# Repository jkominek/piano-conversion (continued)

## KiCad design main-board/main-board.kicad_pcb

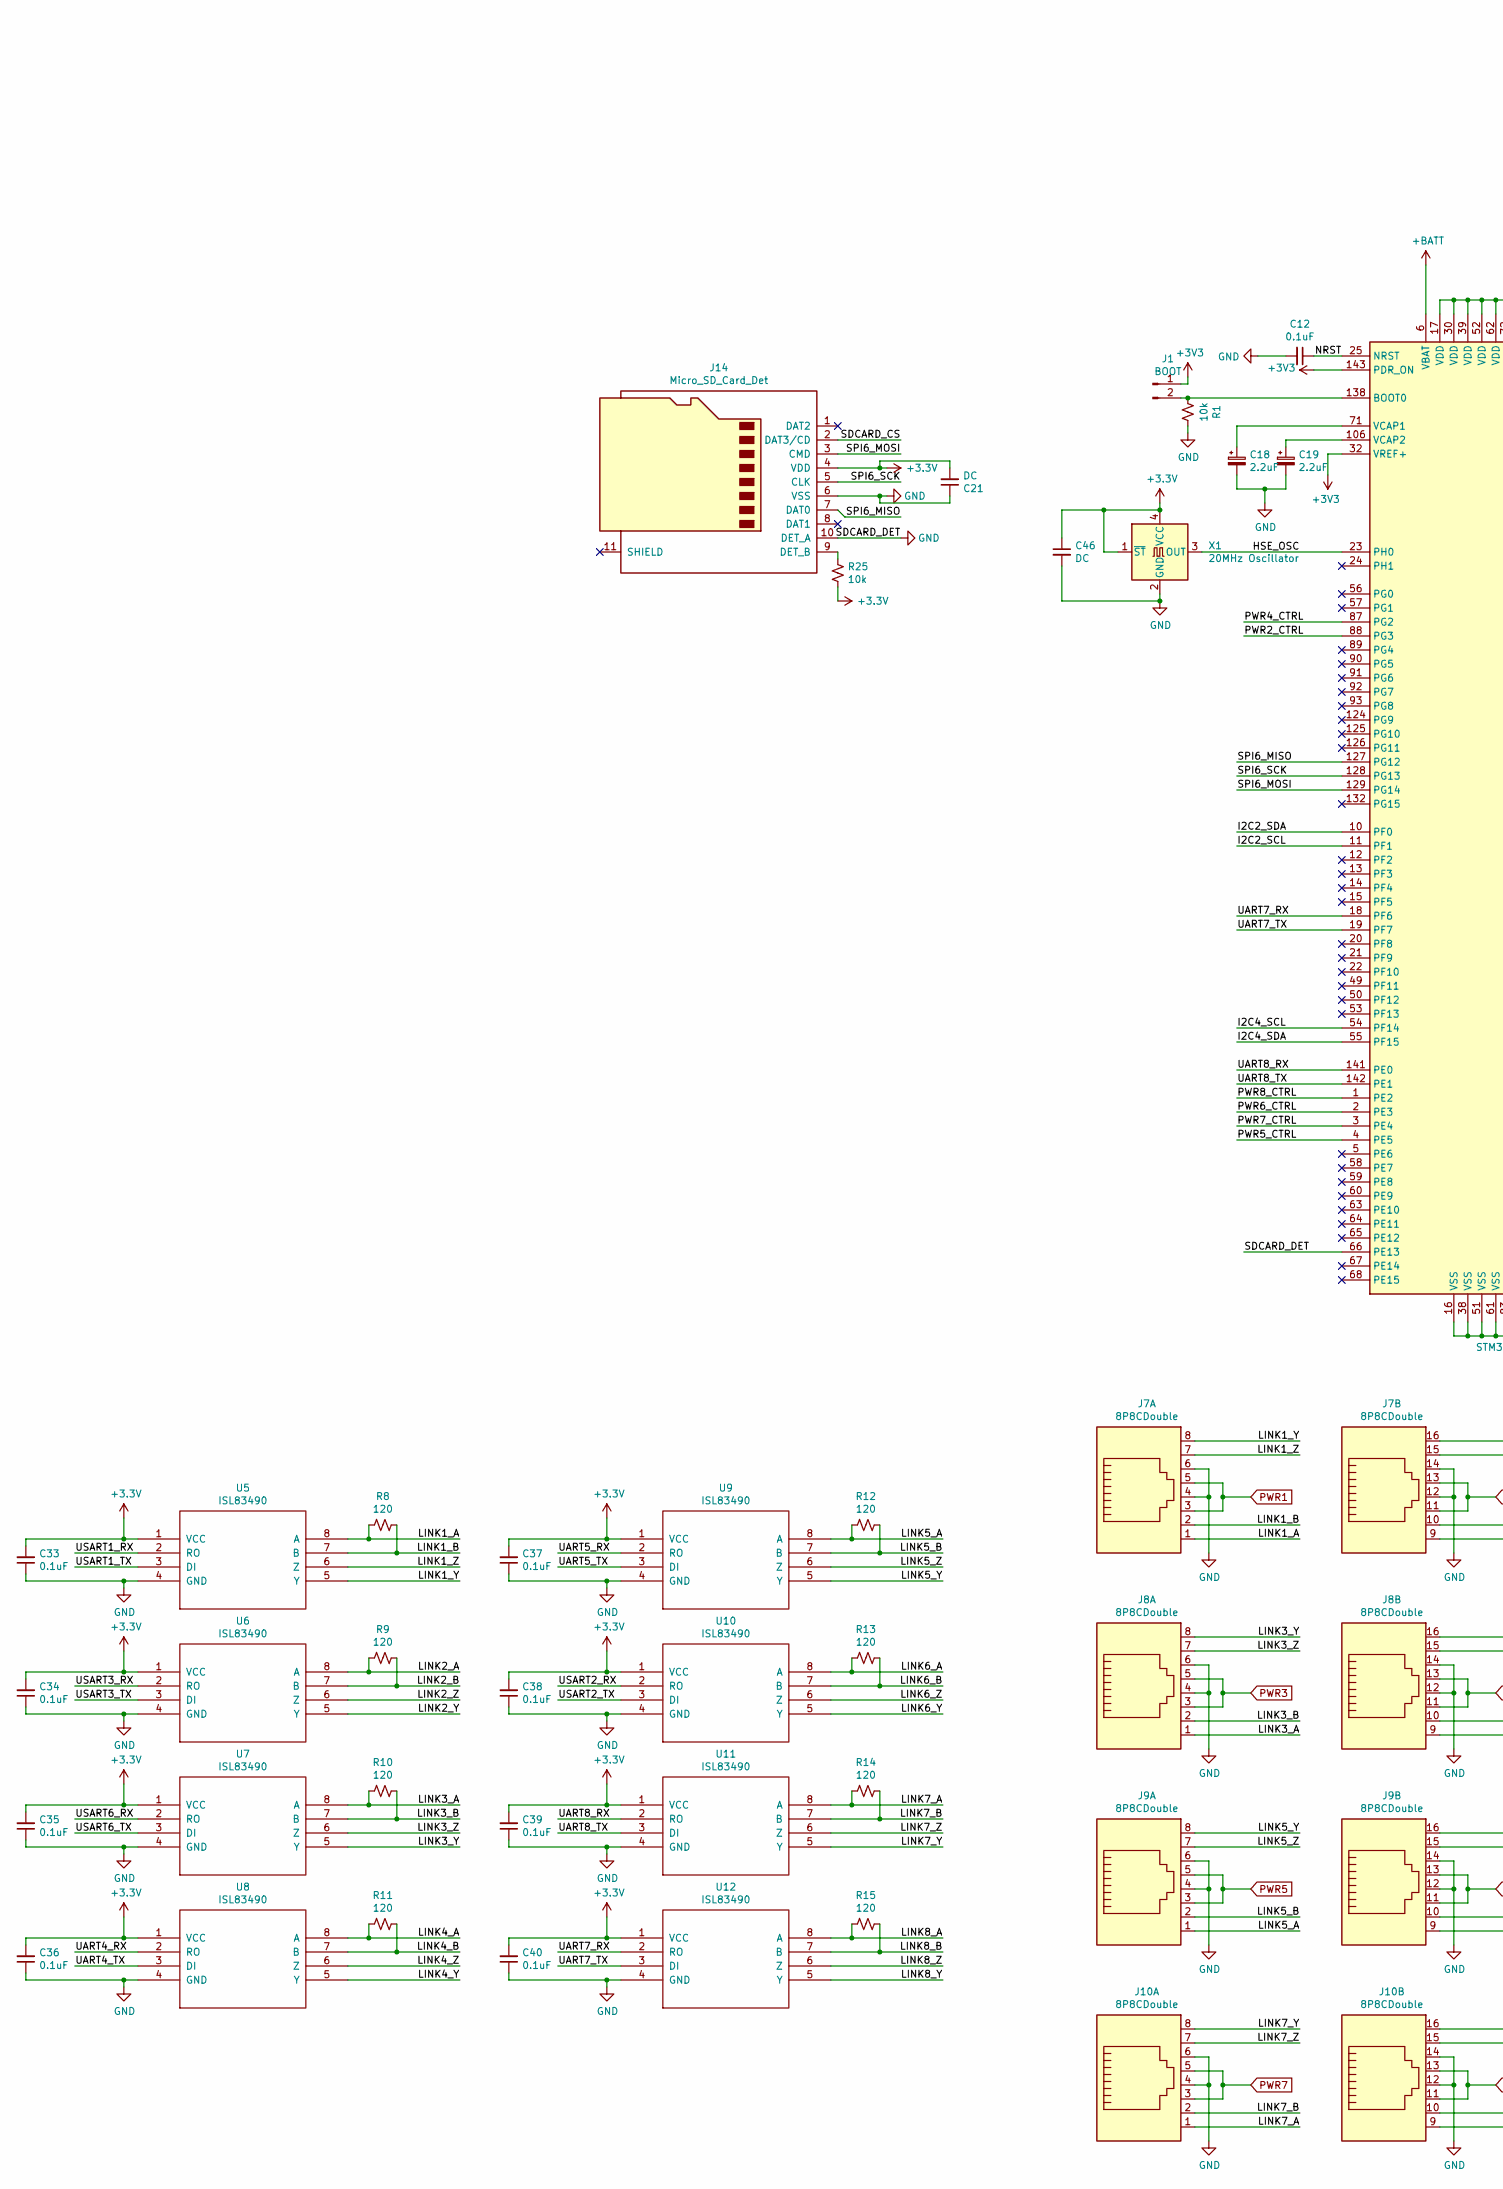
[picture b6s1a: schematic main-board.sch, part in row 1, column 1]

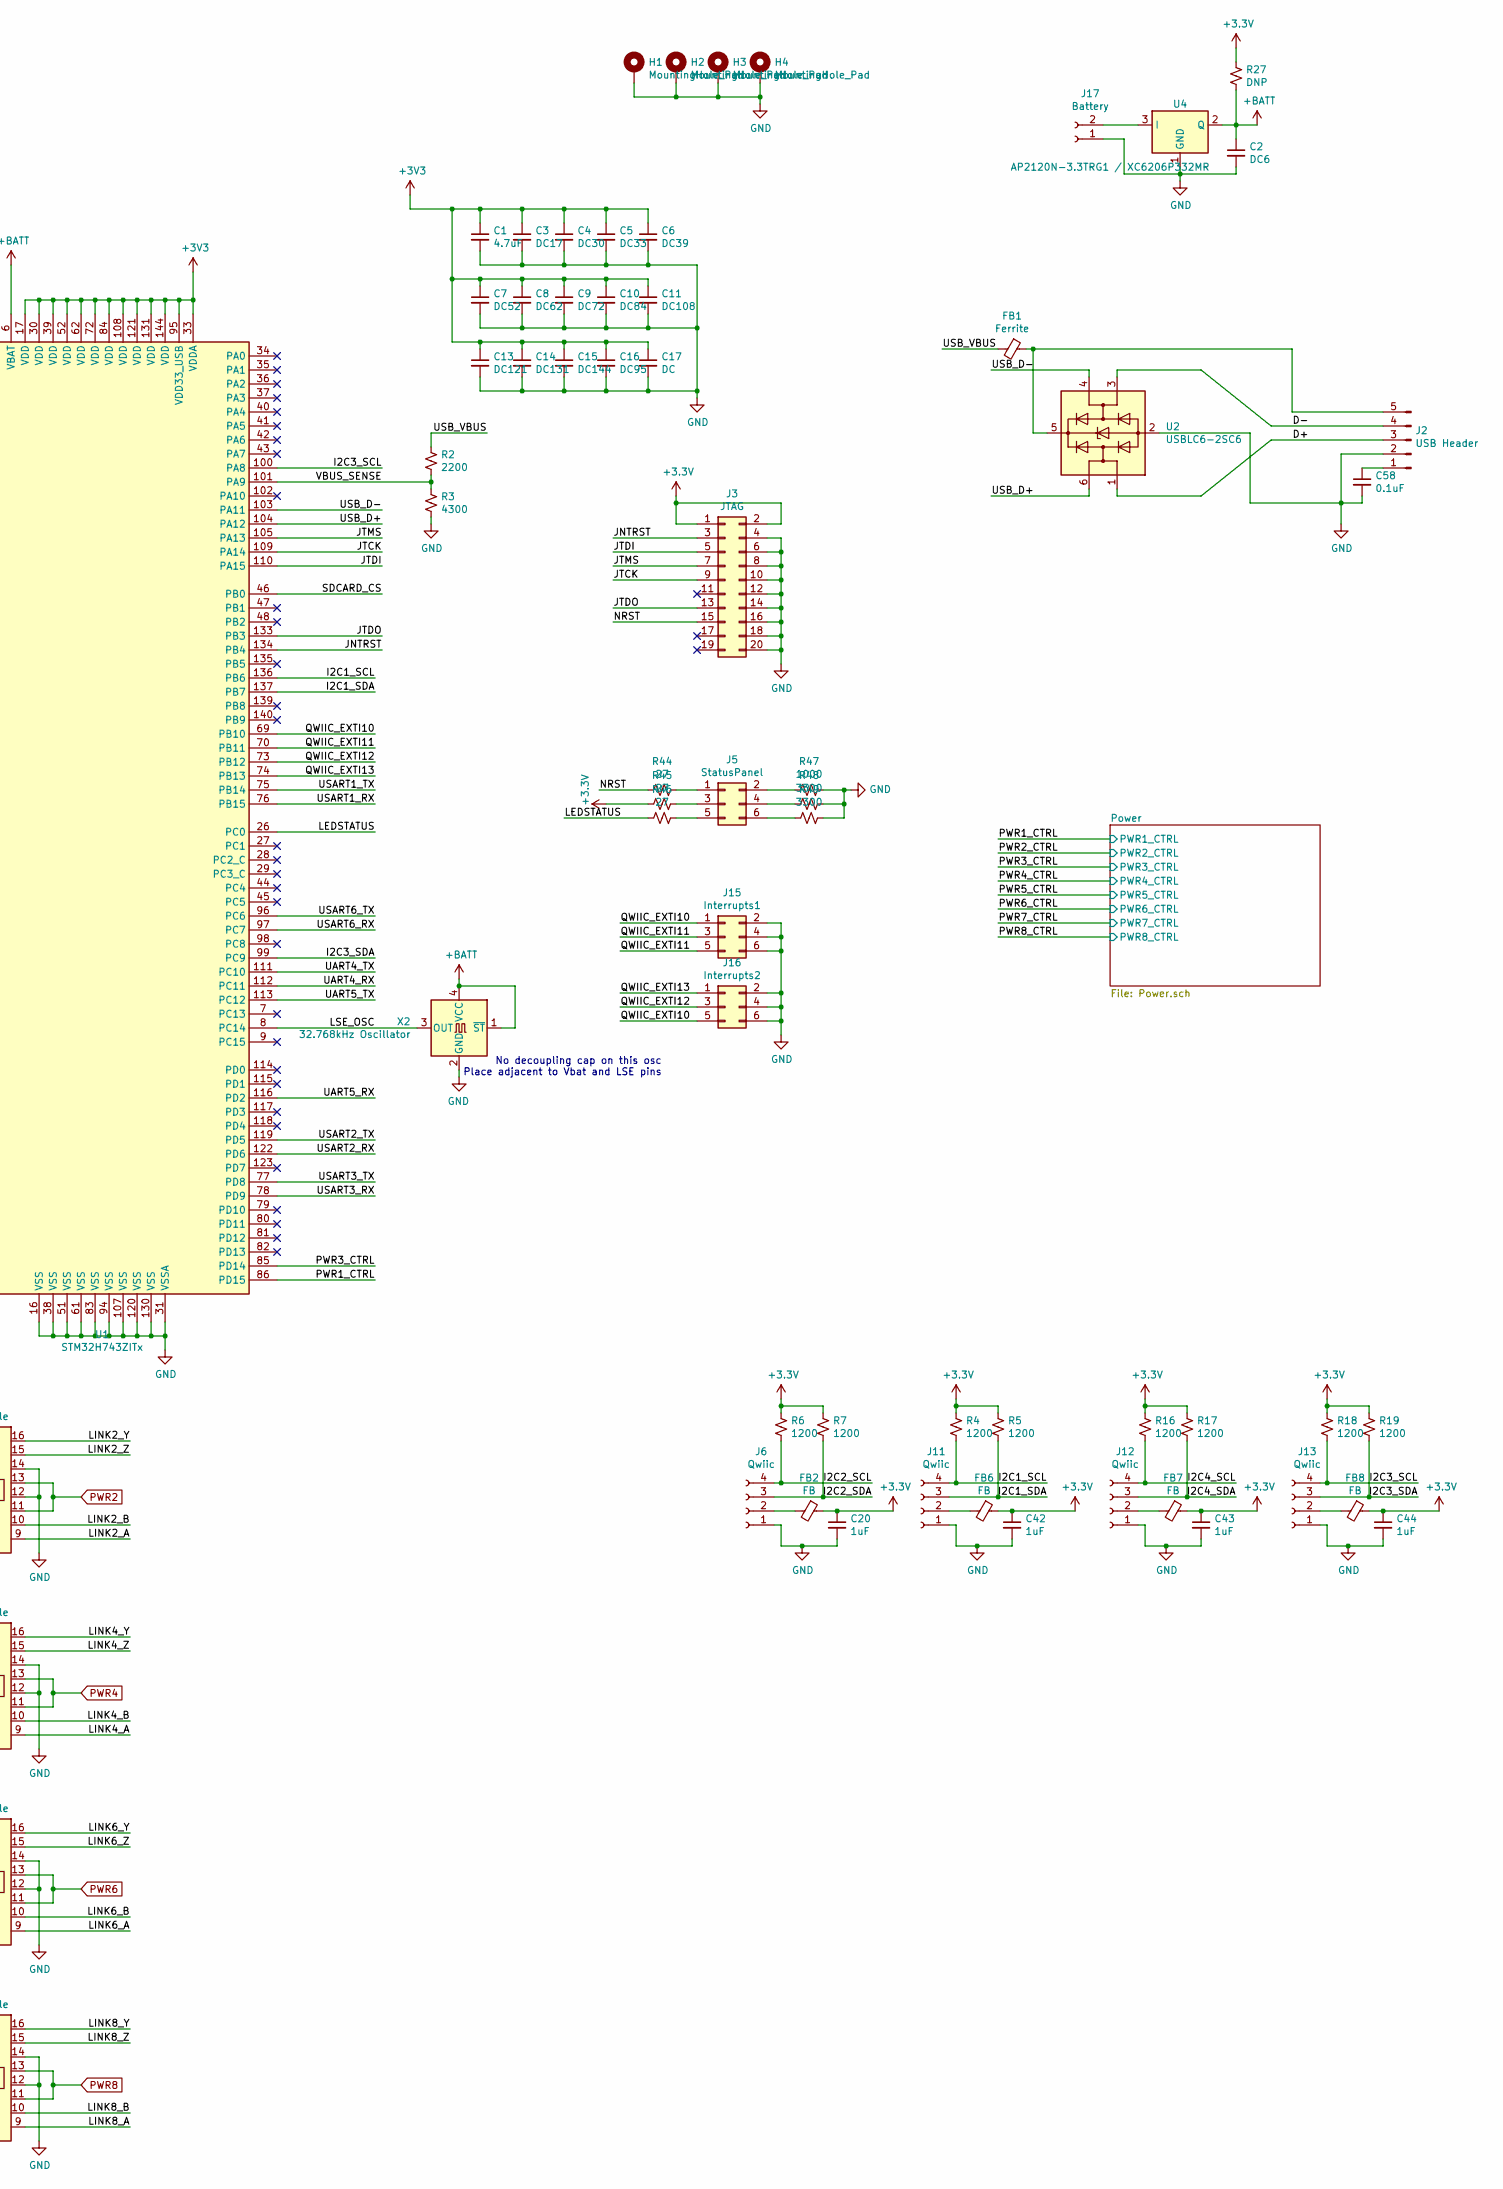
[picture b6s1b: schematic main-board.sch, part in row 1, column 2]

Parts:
C1: 4.7uF; C_0805
C2: DC6; C_0805
C3: DC17; C_0805
C4: DC30; C_0805
C5: DC33; C_0805
C6: DC39; C_0805
C7: DC52; C_0805
C8: DC62; C_0805
C9: DC72; C_0805
C10: DC84; C_0805
C11: DC108; C_0805
C12, C33, C34, C35, C36, C37, C38, C39, C40, C58: 0.1uF; C_0805
C13: DC121; C_0805
C14: DC131; C_0805
C15: DC144; C_0805
C16: DC95; C_0805
C17, C21, C46: DC; C_0805
C18, C19: 2.2uF; C_0805
C20, C42, C43, C44: 1uF; C_0805
FB1: Ferrite; L_0805
FB2, FB6, FB7, FB8: FB; L_0805
H1, H2, H3, H4: MountingHole_Pad; MountingHole_3.2mm_M3_Pad_Via
J1: BOOT; Pin_Header_Straight_1x02_Pitch2.54mm
J2: USB Header; Pin_Header_Straight_1x05_Pitch2.54mm
J3: JTAG; Pin_Header_Straight_2x10_Pitch2.54mm
J5: StatusPanel; Pin_Header_Straight_2x03_Pitch2.54mm
J6, J11, J12, J13: Qwiic; JST_SH_SM04B-SRSS-TB_04x1.00mm_Angled
J7, J8, J9, J10: 8P8CDouble; RJ45_DOUBLE
J14: Micro_SD_Card_Det; 114-00841-68
J15: Interrupts1; Pin_Header_Straight_2x03_Pitch2.54mm
J16: Interrupts2; Pin_Header_Straight_2x03_Pitch2.54mm
J17: Battery; JST_PH_B2B-PH-SM4-TB_02x2.00mm_Straight
R1, R25: 10k; R_0805
R2: 2200; R_0805
R3: 4300; R_0805
R4, R5, R6, R7, R16, R17, R18, R19: 1200; R_0805
R8, R9, R10, R11, R12, R13, R14, R15: 120; R_0805
R27: DNP; R_0805_HandSoldering
R44, R45, R46: 27; R_0805
R47: 1000; R_0805
R48, R49: 3300; R_0805
U1: STM32H743ZITx; LQFP-144_20x20mm_Pitch0.5mm
U2: USBLC6-2SC6; SOT-23-6_Handsoldering
U4: AP2120N-3.3TRG1 / XC6206P332MR; SOT-23
U5, U6, U7, U8, U9, U10, U11, U12: ISL83490; SOIC-8_3.9x4.9mm_Pitch1.27mm
X1: 20MHz Oscillator; Oscillator_SMD_SeikoEpson_SG8002CE-4pin_3.2x2.5mm_HandSolde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
X2: 32.768kHz Oscillator; Oscillator_SMD_SeikoEpson_SG8002CE-4pin_3.2x2.5mm_HandSolde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

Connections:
+BATT: C2.1, R27.2, U1.6 (VBAT), U4.2 (Q), X2.1 (~ST), X2.4 (VCC)
/D+: J2.3, U2.1 (I/O1)
/D-: J2.4, U2.3 (I/O2)
/HSE_OSC: U1.23 (PH0), X1.3 (OUT)
/I2C1_SCL: J11.4, R4.2, U1.136 (PB6)
/I2C1_SDA: J11.3, R5.2, U1.137 (PB7)
/I2C2_SCL: J6.4, R6.2, U1.11 (PF1)
/I2C2_SDA: J6.3, R7.2, U1.10 (PF0)
/I2C3_SCL: J13.4, R18.2, U1.100 (PA8)
/I2C3_SDA: J13.3, R19.2, U1.99 (PC9)
/I2C4_SCL: J12.4, R16.2, U1.54 (PF14)
/I2C4_SDA: J12.3, R17.2, U1.55 (PF15)
/JNTRST: J3.3, U1.134 (PB4)
/JTCK: J3.9, U1.109 (PA14)
/JTDI: J3.5, U1.110 (PA15)
/JTDO: J3.13, U1.133 (PB3)
/JTMS: J3.7, U1.105 (PA13)
/LEDSTATUS: R46.2, U1.26 (PC0)
/LINK1_A: J7.1, R8.2, U5.8 (A)
/LINK1_B: J7.2, R8.1, U5.7 (B)
/LINK1_Y: J7.8, U5.5 (Y)
/LINK1_Z: J7.7, U5.6 (Z)
/LINK2_A: J7.9, R9.2, U6.8 (A)
/LINK2_B: J7.10, R9.1, U6.7 (B)
/LINK2_Y: J7.16, U6.5 (Y)
/LINK2_Z: J7.15, U6.6 (Z)
/LINK3_A: J8.1, R10.2, U7.8 (A)
/LINK3_B: J8.2, R10.1, U7.7 (B)
/LINK3_Y: J8.8, U7.5 (Y)
/LINK3_Z: J8.7, U7.6 (Z)
/LINK4_A: J8.9, R11.2, U8.8 (A)
/LINK4_B: J8.10, R11.1, U8.7 (B)
/LINK4_Y: J8.16, U8.5 (Y)
/LINK4_Z: J8.15, U8.6 (Z)
/LINK5_A: J9.1, R12.2, U9.8 (A)
/LINK5_B: J9.2, R12.1, U9.7 (B)
/LINK5_Y: J9.8, U9.5 (Y)
/LINK5_Z: J9.7, U9.6 (Z)
/LINK6_A: J9.9, R13.2, U10.8 (A)
/LINK6_B: J9.10, R13.1, U10.7 (B)
/LINK6_Y: J9.16, U10.5 (Y)
/LINK6_Z: J9.15, U10.6 (Z)
/LINK7_A: J10.1, R14.2, U11.8 (A)
/LINK7_B: J10.2, R14.1, U11.7 (B)
/LINK7_Y: J10.8, U11.5 (Y)
/LINK7_Z: J10.7, U11.6 (Z)
/LINK8_A: J10.9, R15.2, U12.8 (A)
/LINK8_B: J10.10, R15.1, U12.7 (B)
/LINK8_Y: J10.16, U12.5 (Y)
/LINK8_Z: J10.15, U12.6 (Z)
/LSE_OSC: U1.8 (PC14), X2.3 (OUT)
/NRST: C12.1, J3.15, R44.2, U1.25 (NRST)
/PWR1_CTRL: U1.86 (PD15); also elsewhere on the board
/PWR2_CTRL: U1.88 (PG3); also elsewhere on the board
/PWR3_CTRL: U1.85 (PD14); also elsewhere on the board
/PWR4_CTRL: U1.87 (PG2); also elsewhere on the board
/PWR5_CTRL: U1.4 (PE5); also elsewhere on the board
/PWR6_CTRL: U1.2 (PE3); also elsewhere on the board
/PWR7_CTRL: U1.3 (PE4); also elsewhere on the board
/PWR8_CTRL: U1.1 (PE2); also elsewhere on the board
/QWIIC_EXTI10: J15.1, J16.5, U1.69 (PB10)
/QWIIC_EXTI11: J15.3, J15.5, U1.70 (PB11)
/QWIIC_EXTI12: J16.3, U1.73 (PB12)
/QWIIC_EXTI13: J16.1, U1.74 (PB13)
/SDCARD_CS: J14.2 (DAT3/CD), U1.46 (PB0)
/SPI6_MISO: J14.7 (DAT0), U1.127 (PG12)
/SPI6_MOSI: J14.3 (CMD), U1.129 (PG14)
/SPI6_SCK: J14.5 (CLK), U1.128 (PG13)
/UART4_RX: U1.112 (PC11), U8.2 (RO)
/UART4_TX: U1.111 (PC10), U8.3 (DI)
/UART5_RX: U1.116 (PD2), U9.2 (RO)
/UART5_TX: U1.113 (PC12), U9.3 (DI)
/UART7_RX: U1.18 (PF6), U12.2 (RO)
/UART7_TX: U1.19 (PF7), U12.3 (DI)
/UART8_RX: U1.141 (PE0), U11.2 (RO)
/UART8_TX: U1.142 (PE1), U11.3 (DI)
/USART1_RX: U1.76 (PB15), U5.2 (RO)
/USART1_TX: U1.75 (PB14), U5.3 (DI)
/USART2_RX: U1.122 (PD6), U10.2 (RO)
/USART2_TX: U1.119 (PD5), U10.3 (DI)
/USART3_RX: U1.78 (PD9), U6.2 (RO)
/USART3_TX: U1.77 (PD8), U6.3 (DI)
/USART6_RX: U1.97 (PC7), U7.2 (RO)
/USART6_TX: U1.96 (PC6), U7.3 (DI)
/USB_D+: U1.104 (PA12), U2.6 (I/O1)
/USB_D-: U1.103 (PA11), U2.4 (I/O2)
/USB_VBUS: FB1.2, R2.1
/VBUS_SENSE: R2.2, R3.1, U1.101 (PA9)
GND: C1.2, C2.2, C3.2, C4.2, C5.2, C6.2, C7.2, C8.2, C9.2, C10.2, C11.2, C12.2, C13.2, C14.2, C15.2, C16.2, C17.2, C18.2, C19.2, C20.2, C21.1, C33.1, C34.1, C35.1, C36.1, C37.1, C38.1, C39.1, C40.1, C42.2, C43.2, C44.2, C46.2, C58.2, H1.1, H2.1, H3.1, H4.1, J2.2, J3.4, J3.6, J3.8, J3.10, J3.12, J3.14, J3.16, J3.18, J3.20, J6.1, J7.4, J7.6, J7.12, J7.14, J8.4, J8.6, J8.12, J8.14, J9.4, J9.6, J9.12, J9.14, J10.4, J10.6, J10.12, J10.14, J11.1, J12.1, J13.1, J14.6 (VSS), J14.10 (DET_A), J15.2, J15.4, J15.6, J16.2, J16.4, J16.6, J17.1, R1.1, R3.2, R47.1, R48.1, R49.1, U1.16 (VSS), U1.31 (VSSA), U1.38 (VSS), U1.51 (VSS), U1.61 (VSS), U1.66 (PE13), U1.83 (VSS), U1.94 (VSS), U1.107 (VSS), U1.120 (VSS), U1.130 (VSS), U2.2 (GND), U4.1 (GND), U5.4 (GND), U6.4 (GND), U7.4 (GND), U8.4 (GND), U9.4 (GND), U10.4 (GND), U11.4 (GND), U12.4 (GND), X1.2 (GND), X2.2 (GND); also elsewhere on the board
unnamed: C18.1, U1.71 (VCAP1)
unnamed: C19.1, U1.106 (VCAP2)
unnamed: C58.1, J2.1
unnamed: FB1.1, J2.5, U2.5 (VBUS)
unnamed: FB2.2, J6.2
unnamed: FB6.2, J11.2
unnamed: FB7.2, J12.2
unnamed: FB8.2, J13.2
unnamed: J1.2, R1.2, U1.138 (BOOT0)
unnamed: J5.1, R44.1
unnamed: J5.2, R47.2
unnamed: J5.3, R45.1
unnamed: J5.4, R48.2
unnamed: J5.5, R46.1
unnamed: J5.6, R49.2
unnamed: J14.9 (DET_B), R25.2
unnamed: J17.2, U4.3 (I)
PWR3: J8.3, J8.5; also elsewhere on the board
PWR5: J9.3, J9.5; also elsewhere on the board

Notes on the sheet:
No decoupling cap on this osc Place adjacent to Vbat and LSE pins

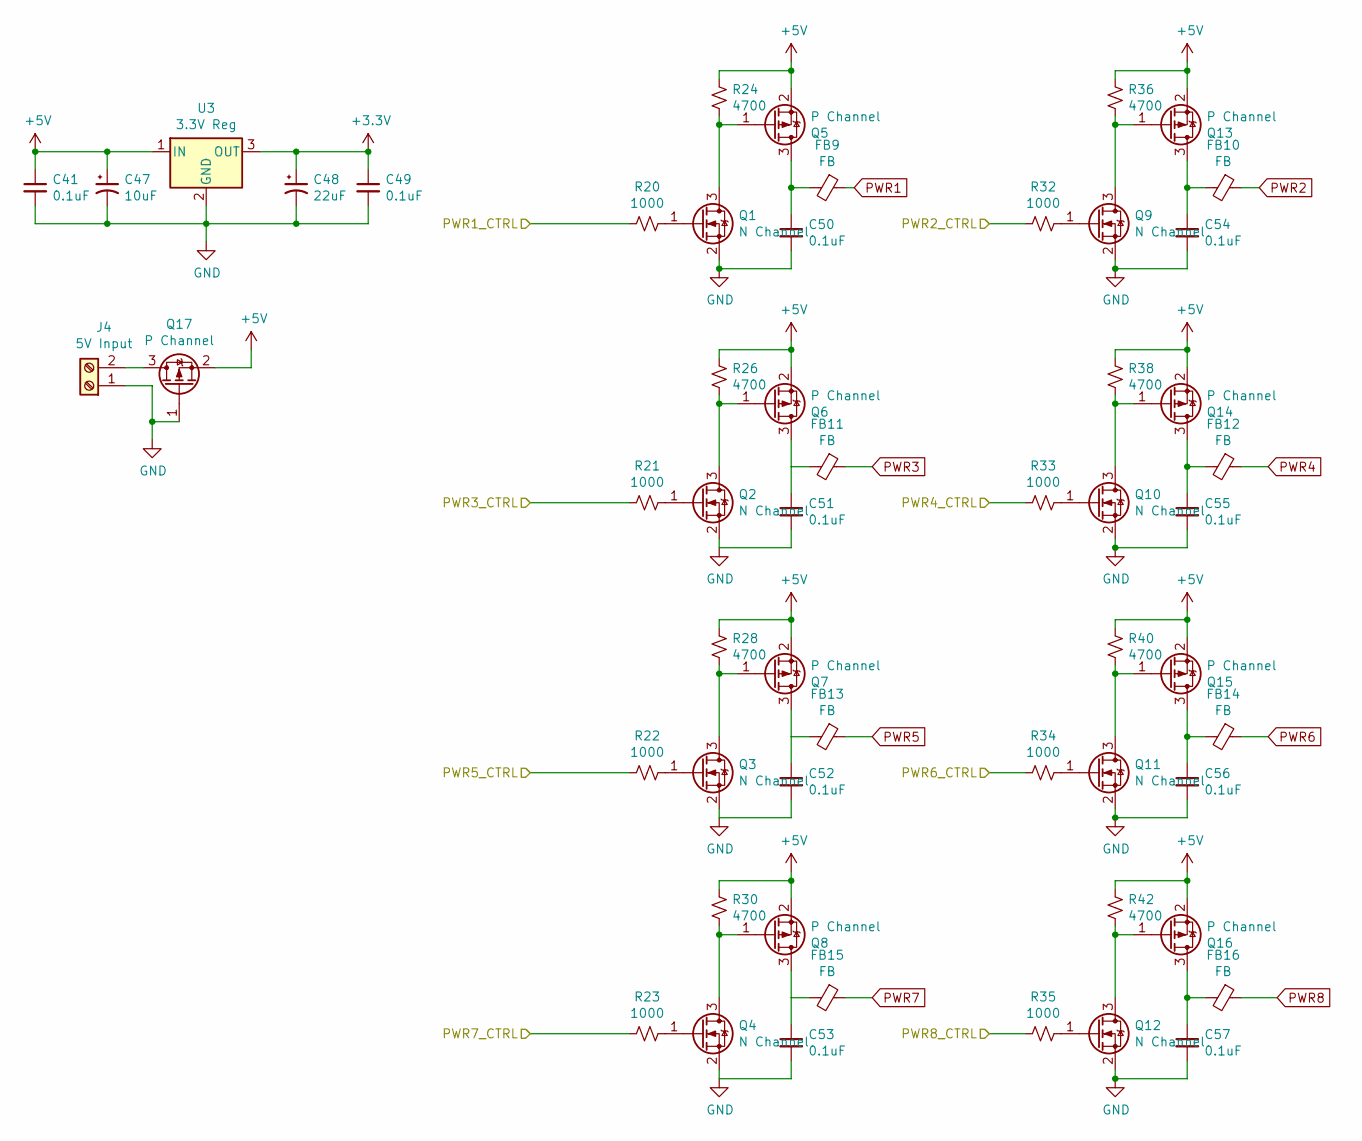
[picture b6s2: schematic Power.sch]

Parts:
C41, C49, C50, C51, C52, C53, C54, C55, C56, C57: 0.1uF; C_0805
C47: 10uF; CP_Elec_4x4.5
C48: 22uF; CP_Elec_5x5.3
FB9, FB10, FB11, FB12, FB13, FB14, FB15, FB16: FB; L_0805
J4: 5V Input; TerminalBlock_bornier-2_P5.08mm
Q1, Q2, Q3, Q4, Q9, Q10, Q11, Q12: N Channel; SOT-323_SC-70_Handsoldering
Q5, Q6, Q7, Q8, Q13, Q14, Q15, Q16, Q17: P Channel; SOT-323_SC-70_Handsoldering
R20, R21, R22, R23, R32, R33, R34, R35: 1000; R_0805
R24, R26, R28, R30, R36, R38, R40, R42: 4700; R_0805
U3: 3.3V Reg; TO-220-3_Vertical

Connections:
+5V: C41.1, C47.1, Q5.2 (S), Q6.2 (S), Q7.2 (S), Q8.2 (S), Q13.2 (S), Q14.2 (S), Q15.2 (S), Q16.2 (S), Q17.2 (S), R24.1, R26.1, R28.1, R30.1, R36.1, R38.1, R40.1, R42.1, U3.1 (IN)
/PWR1_CTRL: R33.2; also elsewhere on the board
/PWR2_CTRL: R20.2; also elsewhere on the board
/PWR3_CTRL: R21.2; also elsewhere on the board
/PWR4_CTRL: R32.2; also elsewhere on the board
/PWR5_CTRL: R22.2; also elsewhere on the board
/PWR6_CTRL: R35.2; also elsewhere on the board
/PWR7_CTRL: R34.2; also elsewhere on the board
/PWR8_CTRL: R23.2; also elsewhere on the board
GND: C41.2, C47.2, C48.2, C49.2, C50.2, C51.2, C52.2, C53.2, C54.2, C55.2, C56.2, C57.2, J4.1, Q1.2 (S), Q2.2 (S), Q3.2 (S), Q4.2 (S), Q9.2 (S), Q10.2 (S), Q11.2 (S), Q12.2 (S), Q17.1 (G), U3.2 (GND); also elsewhere on the board
unnamed: C50.1, FB9.2, Q5.3 (D)
unnamed: C51.1, FB11.2, Q6.3 (D)
unnamed: C52.1, FB13.2, Q7.3 (D)
unnamed: C53.1, FB15.2, Q8.3 (D)
unnamed: C54.1, FB10.2, Q13.3 (D)
unnamed: C55.1, FB12.2, Q14.3 (D)
unnamed: C56.1, FB14.2, Q15.3 (D)
unnamed: C57.1, FB16.2, Q16.3 (D)
unnamed: J4.2, Q17.3 (D)
unnamed: Q1.1 (G), R20.1
unnamed: Q1.3 (D), Q5.1 (G), R24.2
unnamed: Q2.1 (G), R21.1
unnamed: Q2.3 (D), Q6.1 (G), R26.2
unnamed: Q3.1 (G), R22.1
unnamed: Q3.3 (D), Q7.1 (G), R28.2
unnamed: Q4.1 (G), R23.1
unnamed: Q4.3 (D), Q8.1 (G), R30.2
unnamed: Q9.1 (G), R32.1
unnamed: Q10.1 (G), R33.1
unnamed: Q10.3 (D), Q14.1 (G), R38.2
unnamed: Q11.1 (G), R34.1
unnamed: Q11.3 (D), Q15.1 (G), R40.2
unnamed: Q12.1 (G), R35.1
unnamed: Q12.3 (D), Q16.1 (G), R42.2
unnamed: Q9.3 (D), Q13.1 (G), R36.2
PWR3: FB11.1; also elsewhere on the board
PWR5: FB13.1; also elsewhere on the board

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
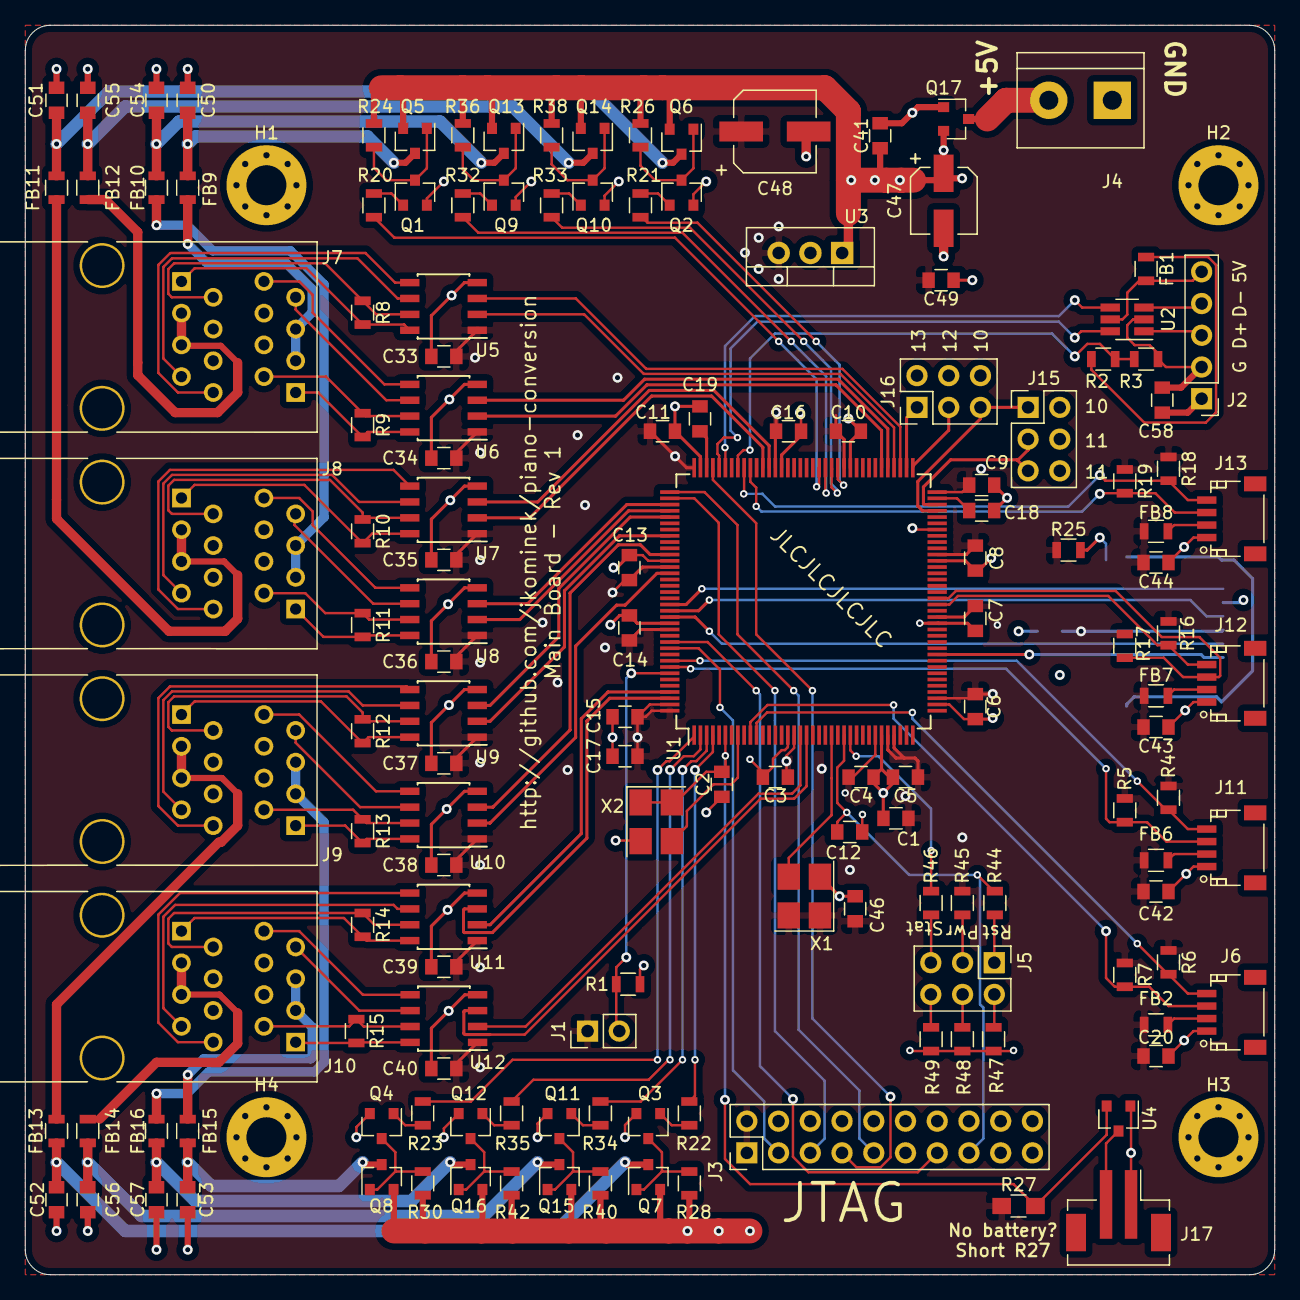
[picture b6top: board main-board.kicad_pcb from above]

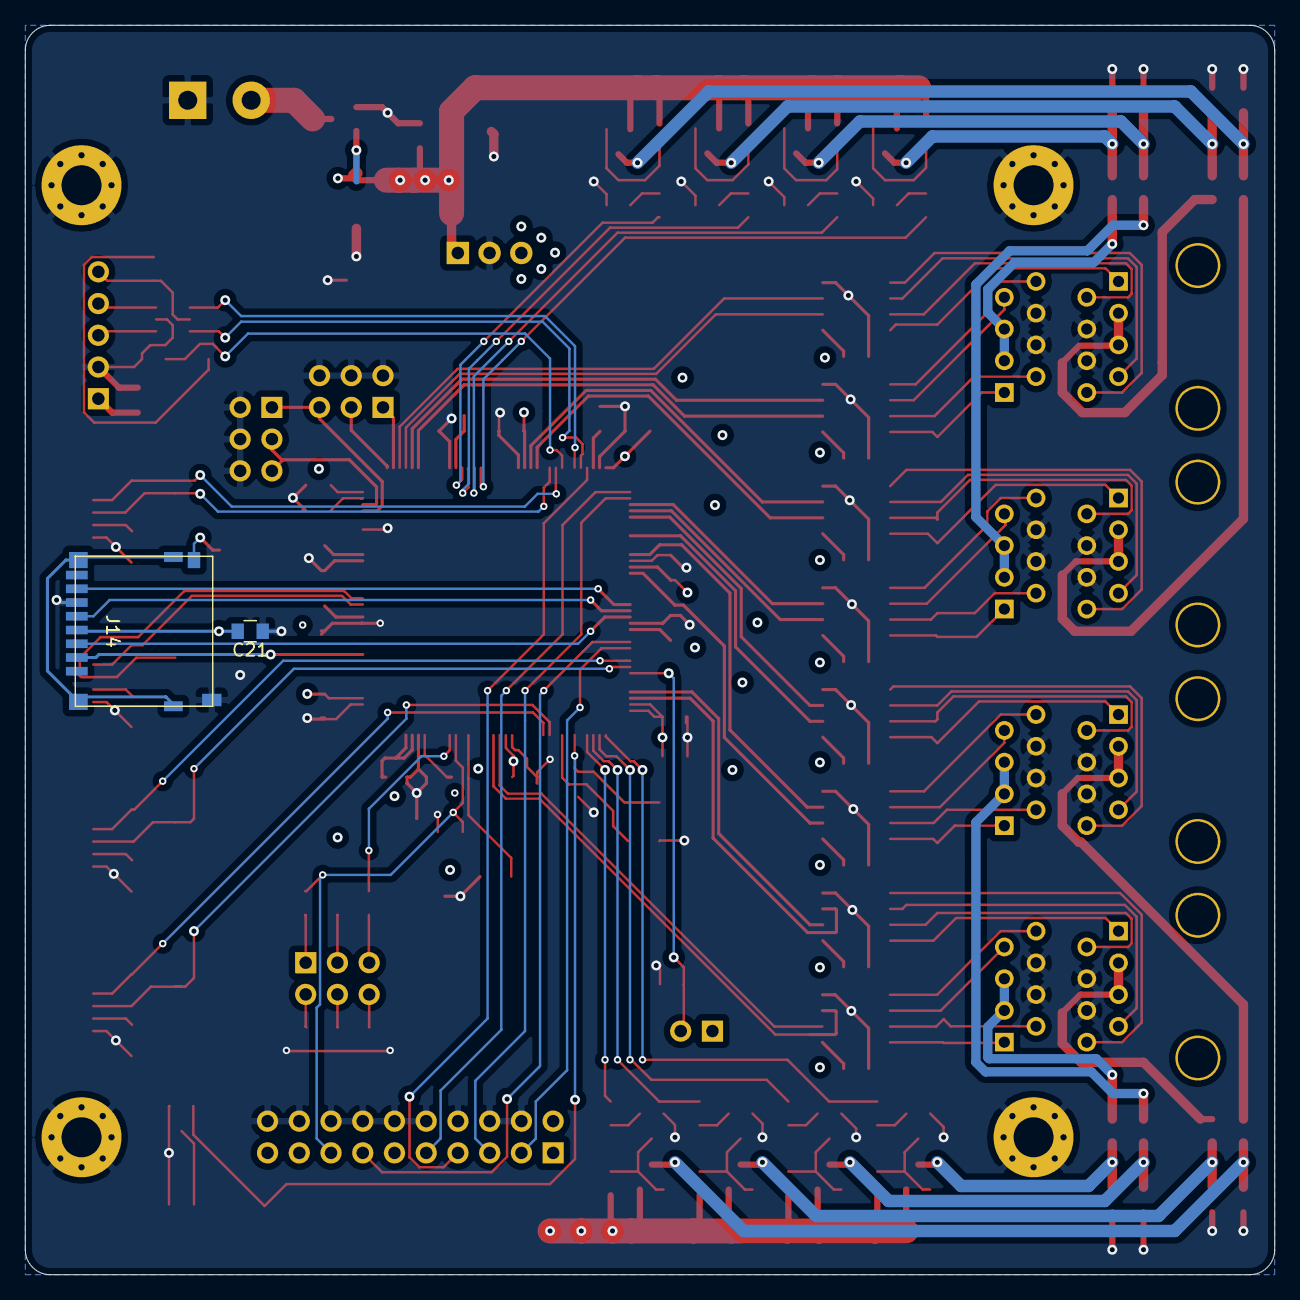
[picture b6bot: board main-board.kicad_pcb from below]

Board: 4 copper layers, 100.0 x 100.0 mm, 154 parts (2 on the bottom side), 141 nets.

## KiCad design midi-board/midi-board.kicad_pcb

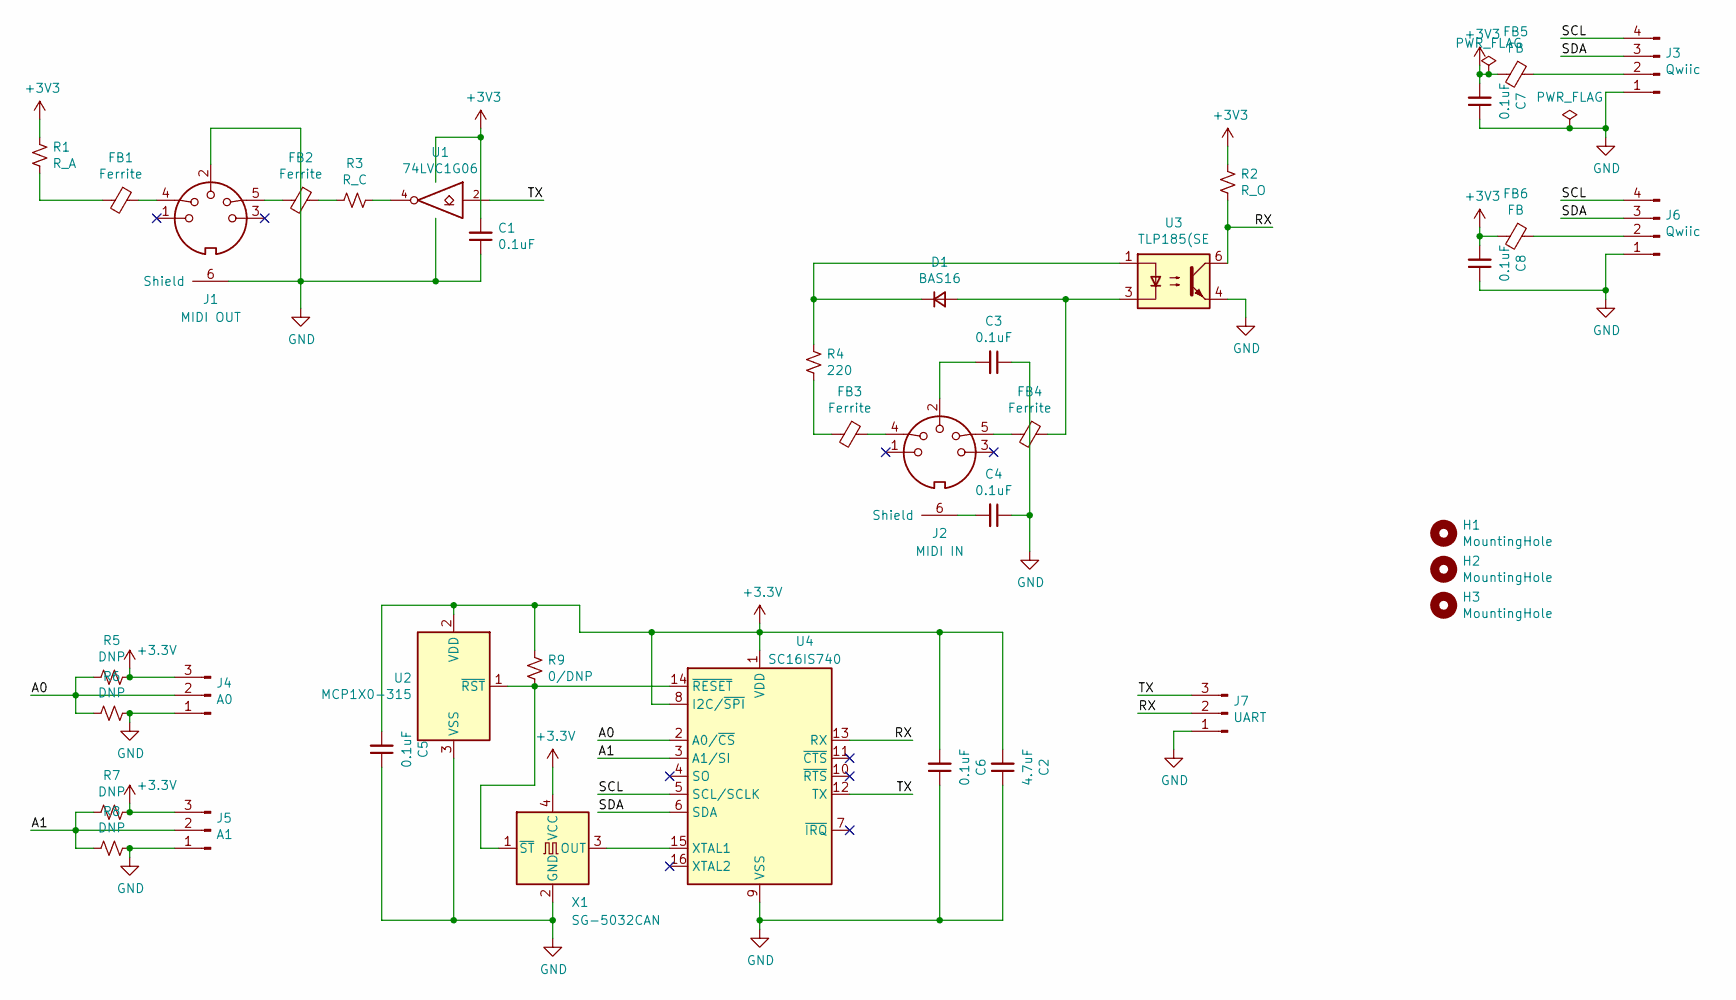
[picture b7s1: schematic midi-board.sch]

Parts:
C1, C3, C4, C5, C6, C7, C8: 0.1uF; C_0805_HandSoldering
C2: 4.7uF; C_0805_HandSoldering
D1: BAS16; D_SOT-23_ANK
FB1, FB2, FB3, FB4: Ferrite; L_0805_HandSoldering
FB5, FB6: FB; L_0805_HandSoldering
H1, H2, H3: MountingHole; MountingHole_3.2mm_M3
J1: MIDI OUT; SDS-50J
J2: MIDI IN; SDS-50J
J3, J6: Qwiic; JST_SH_SM04B-SRSS-TB_04x1.00mm_Angled
J4: A0; Pin_Header_Straight_1x03_Pitch2.54mm
J5: A1; Pin_Header_Straight_1x03_Pitch2.54mm
J7: UART; Pin_Header_Straight_1x03_Pitch2.54mm
R1: R_A; R_0805_HandSoldering
R2: R_O; R_0805_HandSoldering
R3: R_C; R_0805_HandSoldering
R4: 220; R_0805_HandSoldering
R5, R6, R7, R8: DNP; R_0805_HandSoldering
R9: 0/DNP; R_0805_HandSoldering
U1: 74LVC1G06; SOT-353_SC-70-5_Handsoldering
U2: MCP1X0-315; SOT-23
U3: TLP185(SE; SO-6_4.4x3.6mm_Pitch1.27mm
U4: SC16IS740; TSSOP-16_4.4x5mm_Pitch0.65mm
X1: SG-5032CAN; Oscillator_SMD_SeikoEpson_SG8002CE-4pin_3.2x2.5mm_HandSolde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

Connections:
/A0: J4.2, R5.2, R6.2, U4.2 (A0/~CS)
/A1: J5.2, R7.2, R8.2, U4.3 (A1/SI)
/CLK: U4.15 (XTAL1), X1.3 (OUT)
/RX: J7.2, R2.2, U3.6, U4.13 (RX)
/SCL: J3.4, J6.4, U4.5 (SCL/SCLK); also elsewhere on the board
/SDA: J3.3, J6.3, U4.6 (SDA); also elsewhere on the board
/TX: J7.3, U1.2, U4.12 (TX)
/~IRQ: U4.7 (~IRQ); also elsewhere on the board
/~RST: R9.1, U2.1 (~RST), U4.14 (~RESET), X1.1 (~ST)
GND: C1.1, C2.1, C3.1, C4.1, C5.1, C6.1, C7.1, C8.1, J1.2, J1.6 (Shield), J3.1, J4.1, J5.1, J6.1, J7.1, R6.1, R8.1, U1.3 (GND), U2.3 (VSS), U3.4, U4.9 (VSS), X1.2 (GND); also elsewhere on the board
unnamed: C3.2, J2.2
unnamed: C4.2, J2.6 (Shield)
unnamed: D1.1 (K), R4.1, U3.1
unnamed: D1.2 (A), FB4.1, U3.3
unnamed: FB1.1, J1.4
unnamed: FB1.2, R1.2
unnamed: FB2.1, R3.2
unnamed: FB2.2, J1.5
unnamed: FB3.1, J2.4
unnamed: FB3.2, R4.2
unnamed: FB4.2, J2.5
unnamed: FB5.1, J3.2
unnamed: FB6.1, J6.2
unnamed: R3.1, U1.4

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
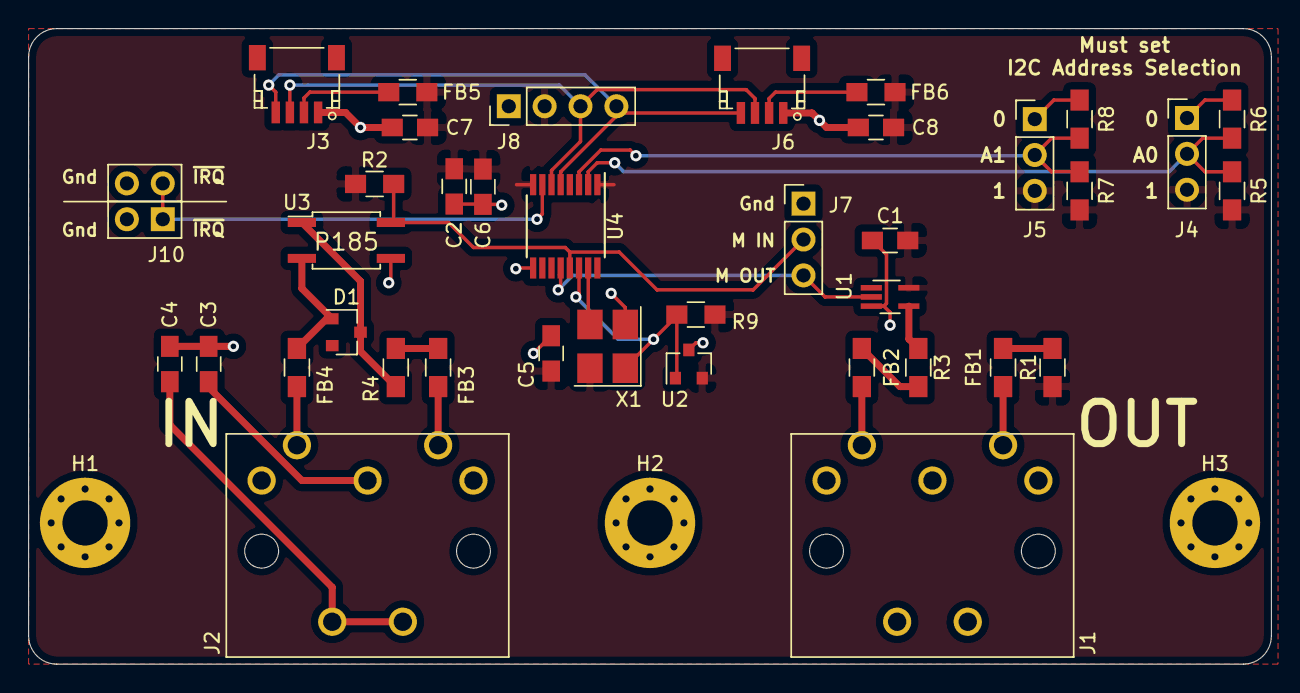
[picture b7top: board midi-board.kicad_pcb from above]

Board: 2 copper layers, 88.0 x 45.0 mm, 41 parts (0 on the bottom side), 25 nets.

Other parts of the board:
J8: I2C; Pin_Header_Straight_1x04_Pitch2.54mm
J10: Conn_02x02_Odd_Even; Pin_Header_Straight_2x02_Pitch2.54mm

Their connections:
/SCL: J8.4; also elsewhere on the board
/SDA: J8.3; also elsewhere on the board
/~IRQ: J10.1, J10.3; also elsewhere on the board
GND: J8.1, J10.2, J10.4; also elsewhere on the board

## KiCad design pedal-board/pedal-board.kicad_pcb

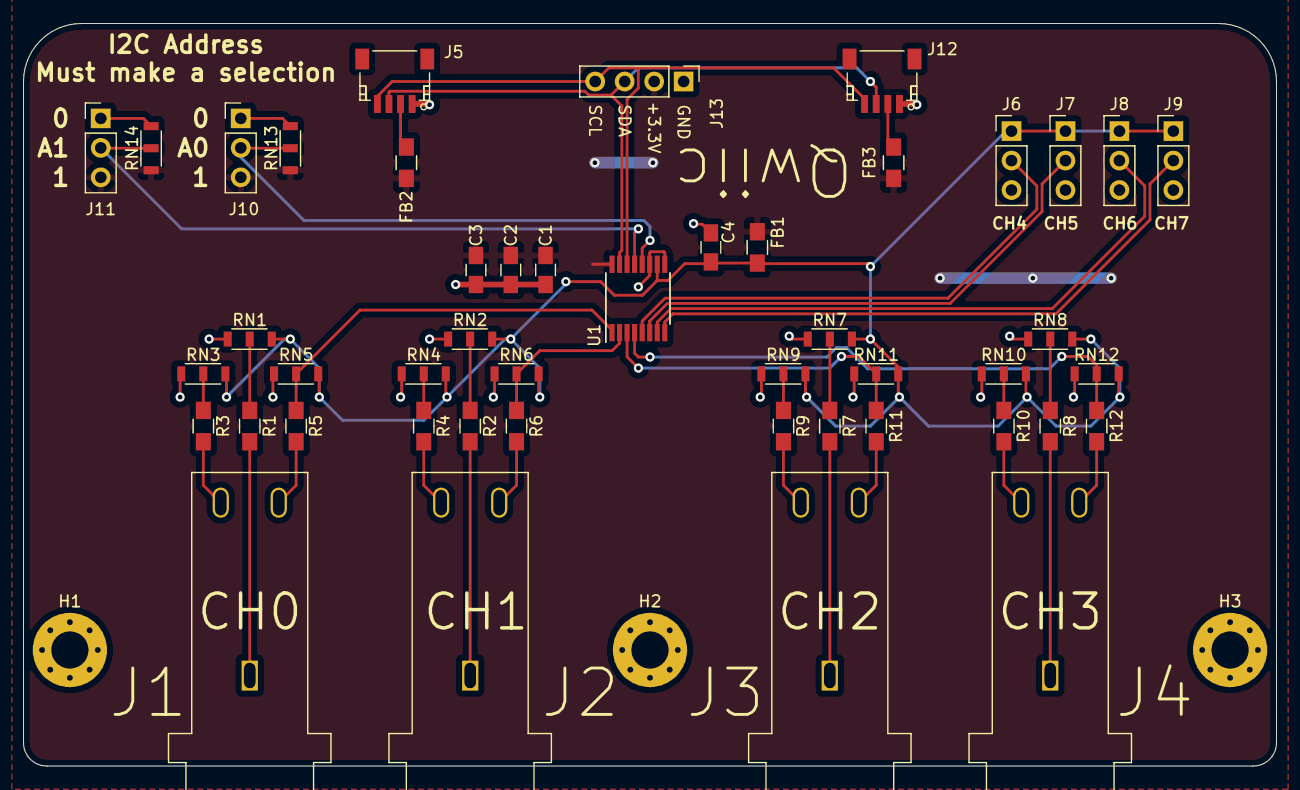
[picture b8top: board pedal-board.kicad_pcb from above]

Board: 2 copper layers, 108.0 x 64.0 mm, 50 parts (0 on the bottom side), 37 nets.

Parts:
C1, C4: 0.1uF; C_0805_HandSoldering
C2: 1uF; C_0805_HandSoldering
C3: 4.7uF; C_0805_HandSoldering
FB1, FB2, FB3: FB; L_0805_HandSoldering
H1, H2, H3: MountingHole_Pad; MountingHole_3.2mm_M3_Pad_Via
J1: AudioJack0; SJ-63053A
J2: AudioJack1; SJ-63053A
J3: AudioJack2; SJ-63053A
J4: AudioJack3; SJ-63053A
J5, J12: Qwiic; JST_SH_SM04B-SRSS-TB_04x1.00mm_Angled
J6, J7, J8, J9, J10, J11: CH7; Pin_Header_Straight_1x03_Pitch2.54mm
J13: Qwiic; Pin_Header_Straight_1x04_Pitch2.54mm
R1, R2, R3, R4, R5, R6, R7, R8, R9, R10, R11, R12: 10; R_0805_HandSoldering
RN1, RN2, RN3, RN4, RN5, RN6, RN7, RN8, RN9, RN10, RN11, RN12, RN13, RN14: Div; R_0805_Divider
U1: ADS7830; TSSOP-16_4.4x5mm_Pitch0.65mm

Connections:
+3.3VA: C4.1, FB1.2, J6.1, J7.1, J8.1, J9.1, RN1.3, RN2.3, RN3.3, RN4.3, RN5.3, RN6.3, RN7.3, RN8.3, RN9.3, RN10.3, RN11.3, RN12.3, U1.10
+3V3: C1.1, C2.1, C3.1, FB1.1, FB2.1, FB3.1, J10.3, J11.3, J13.2, RN13.1, RN14.1, U1.16
/A0: J10.2, RN13.2, U1.12
/A1: J11.2, RN14.2, U1.13
/CH0: R5.1, RN5.2, U1.1
/CH1: R6.1, RN6.2, U1.2
/CH2: R11.1, RN11.2, U1.3
/CH3: R12.1, RN12.2, U1.4
/SCL: J5.4, J12.4, J13.4, U1.14
/SDA: J5.3, J12.3, J13.3, U1.15
GND: C1.2, C2.2, C3.2, C4.2, H1.1, H2.1, H3.1, J5.1, J6.3, J7.3, J8.3, J9.3, J10.1, J11.1, J12.1, J13.1, RN1.1, RN2.1, RN3.1, RN4.1, RN5.1, RN6.1, RN7.1, RN8.1, RN9.1, RN10.1, RN11.1, RN12.1, RN13.3, RN14.3, U1.9, U1.11
unnamed: FB2.2, J5.2
unnamed: FB3.2, J12.2
unnamed: J1.R, R3.2
unnamed: J1.S, R1.2
unnamed: J1.T, R5.2
unnamed: J2.R, R4.2
unnamed: J2.S, R2.2
unnamed: J2.T, R6.2
unnamed: J3.R, R9.2
unnamed: J3.S, R7.2
unnamed: J3.T, R11.2
unnamed: J4.R, R10.2
unnamed: J4.S, R8.2
unnamed: J4.T, R12.2
unnamed: J6.2, U1.5
unnamed: J7.2, U1.6
unnamed: J8.2, U1.7
unnamed: J9.2, U1.8
unnamed: R1.1, RN1.2
unnamed: R2.1, RN2.2
unnamed: R3.1, RN3.2
unnamed: R4.1, RN4.2
unnamed: R7.1, RN7.2
unnamed: R8.1, RN8.2
unnamed: R9.1, RN9.2
unnamed: R10.1, RN10.2
